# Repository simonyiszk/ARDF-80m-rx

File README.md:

# ARDF-80m-rx
Rókavevő a 80m-es rádióamatőr sávra (3579 kHz fix frekvenciájú)

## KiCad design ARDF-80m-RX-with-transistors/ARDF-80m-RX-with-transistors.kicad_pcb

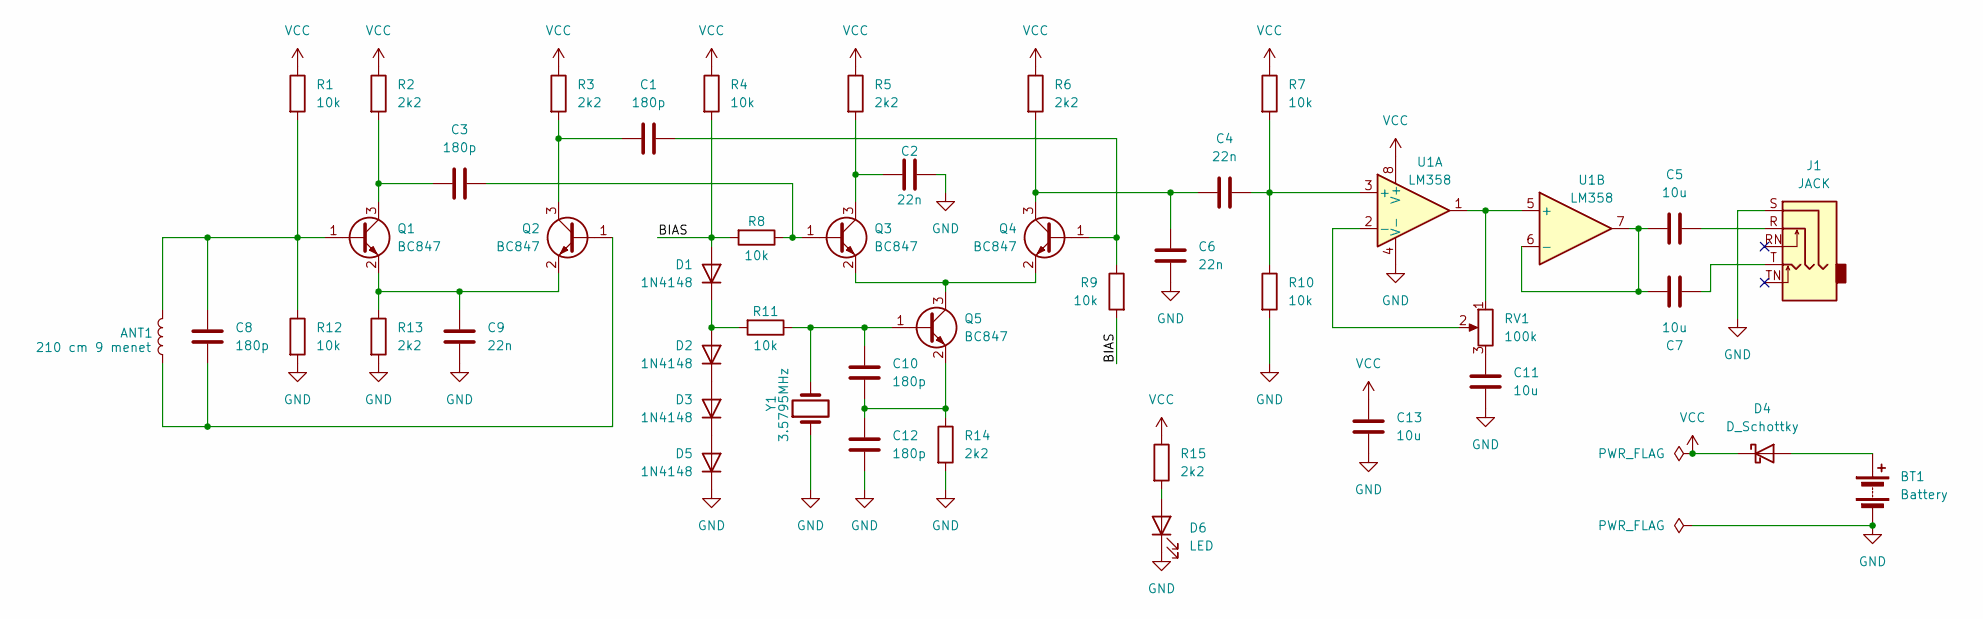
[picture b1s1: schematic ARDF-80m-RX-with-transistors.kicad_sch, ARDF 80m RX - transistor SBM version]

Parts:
ANT1: 210 cm 9 menet; PinHeader_2x01_P2.54mm_Vertical
BT1: Battery; PinHeader_2x01_P2.54mm_Vertical
C1, C3, C8, C10, C12: 180p; C_0805_2012Metric_Pad1.18x1.45mm_HandSolder
C2, C4, C6, C9: 22n; C_0805_2012Metric_Pad1.18x1.45mm_HandSolder
C5, C7, C11, C13: 10u; C_0805_2012Metric_Pad1.18x1.45mm_HandSolder
D1, D2, D3, D5: 1N4148; D_0805_2012Metric_Pad1.15x1.40mm_HandSolder
D4: D_Schottky; D_SMB_Handsoldering
D6: LED; LED_D3.0mm
J1: JACK; Jack_3.5mm_CUI_SJ1-3525N_Horizontal
Q1, Q2, Q3, Q4, Q5: BC847; SOT-23
R1, R4, R7, R8, R9, R10, R11, R12: 10k; R_0805_2012Metric_Pad1.20x1.40mm_HandSolder
R2, R3, R5, R6, R13, R14, R15: 2k2; R_0805_2012Metric_Pad1.20x1.40mm_HandSolder
RV1: 100k; Potentiometer_ACP_CA9-V10_Vertical
U1: LM358; SOIC-8_3.9x4.9mm_P1.27mm
Y1: 3.5795MHz; Crystal_HC49-4H_Vertical

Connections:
/BIAS: D1.2 (A), R4.2, R8.2, R9.2
GND: BT1.2 (-), C2.2, C6.2, C9.2, C11.2, C12.2, C13.1, D5.1 (K), D6.1 (K), J1.S, R10.2, R12.2, R13.2, R14.2, U1.4 (V-), Y1.1
unnamed: BT1.1 (+), D4.2 (A)
unnamed: C5.2, J1.R
unnamed: C7.1, J1.T
unnamed: C11.1, RV1.3
unnamed: D1.1 (K), D2.2 (A), R11.2
unnamed: D2.1 (K), D3.2 (A)
unnamed: D3.1 (K), D5.2 (A)
unnamed: D6.2 (A), R15.2
unnamed: ANT1.2, C8.1, Q1.1 (B), R1.2, R12.1
unnamed: C3.2, Q1.3 (C), R2.2
unnamed: C9.1, Q1.2 (E), Q2.2 (E), R13.1
unnamed: ANT1.1, C8.2, Q2.1 (B)
unnamed: C1.1, Q2.3 (C), R3.2
unnamed: C3.1, Q3.1 (B), R8.1
unnamed: C2.1, Q3.3 (C), R5.2
unnamed: Q3.2 (E), Q4.2 (E), Q5.3 (C)
unnamed: C1.2, Q4.1 (B), R9.1
unnamed: C4.1, C6.1, Q4.3 (C), R6.2
unnamed: C10.1, Q5.1 (B), R11.1, Y1.2
unnamed: C10.2, C12.1, Q5.2 (E), R14.1
unnamed: C4.2, R7.2, R10.1, U1.3 (+)
unnamed: RV1.2, U1.2 (-)
unnamed: RV1.1, U1.1, U1.5 (+)
unnamed: C5.1, C7.2, U1.6 (-), U1.7
VCC: C13.2, D4.1 (K), R1.1, R2.1, R3.1, R4.1, R5.1, R6.1, R7.1, R15.1, U1.8 (V+)

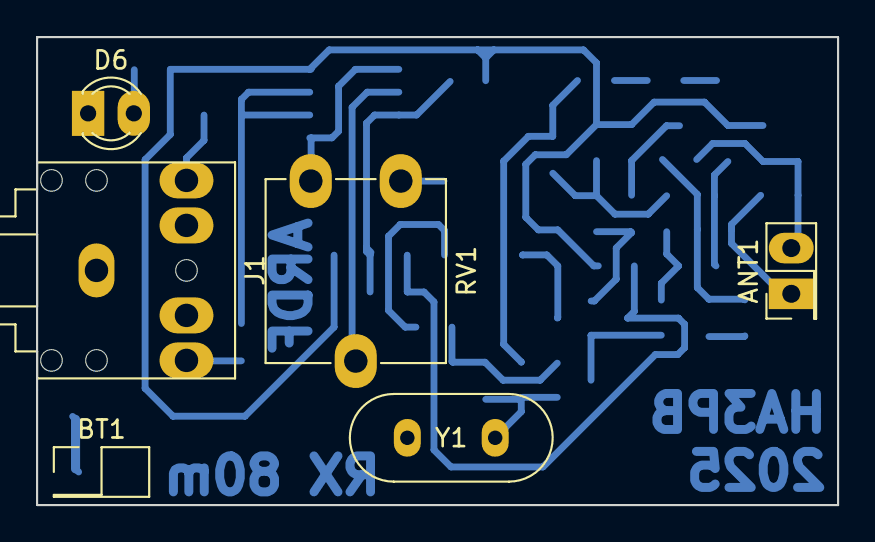
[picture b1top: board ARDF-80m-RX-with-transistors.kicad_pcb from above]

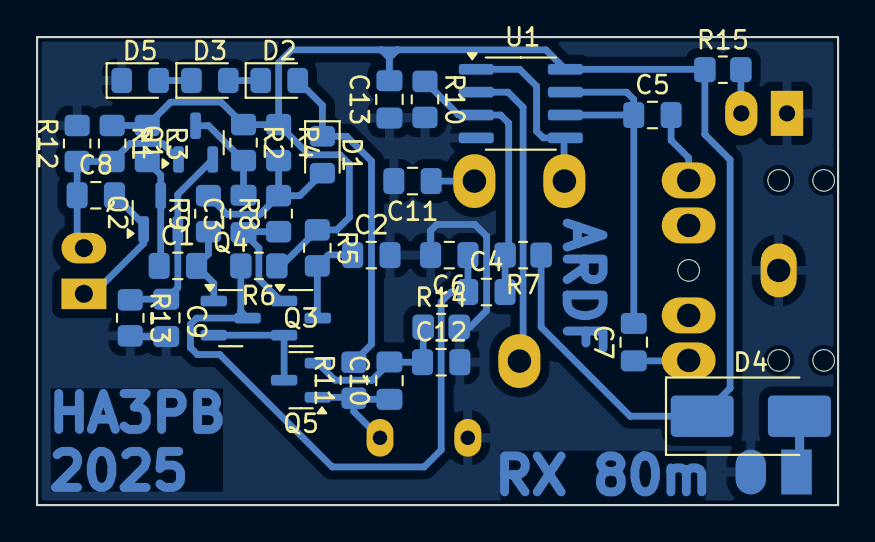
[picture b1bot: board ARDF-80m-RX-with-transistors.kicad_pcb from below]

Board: 2 copper layers, 44.5 x 26.0 mm, 45 parts (39 on the bottom side), 27 nets.

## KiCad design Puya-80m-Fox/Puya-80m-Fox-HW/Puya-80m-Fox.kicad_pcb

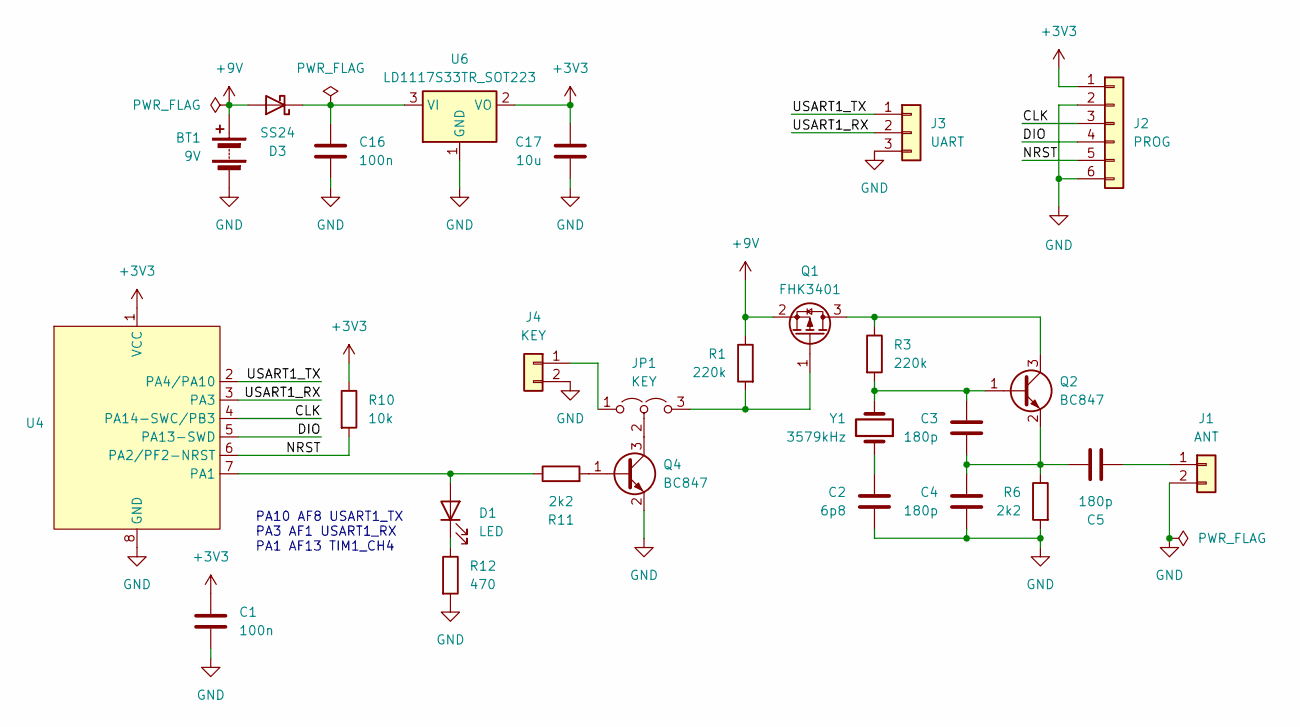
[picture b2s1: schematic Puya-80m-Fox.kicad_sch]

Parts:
BT1: 9V; PinHeader_1x02_P2.54mm_Vertical
C1, C16: 100n; C_0805_2012Metric_Pad1.18x1.45mm_HandSolder
C2: 6p8; C_0805_2012Metric_Pad1.18x1.45mm_HandSolder
C3, C4, C5: 180p; C_0805_2012Metric_Pad1.18x1.45mm_HandSolder
C17: 10u; C_0805_2012Metric_Pad1.18x1.45mm_HandSolder
D1: LED; LED_0805_2012Metric_Pad1.15x1.40mm_HandSolder
D3: SS24; D_SMA
J1: ANT; PinHeader_1x02_P2.54mm_Vertical
J2: PROG; PinHeader_1x06_P2.54mm_Vertical
J3: UART; PinHeader_1x03_P2.54mm_Vertical
J4: KEY; PinHeader_1x02_P2.54mm_Vertical
JP1: KEY; SolderJumper-3_P1.3mm_Open_RoundedPad1.0x1.5mm
Q1: FHK3401; SOT-23
Q2, Q4: BC847; SOT-23
R1, R3: 220k; R_0805_2012Metric_Pad1.20x1.40mm_HandSolder
R6, R11: 2k2; R_0805_2012Metric_Pad1.20x1.40mm_HandSolder
R10: 10k; R_0805_2012Metric_Pad1.20x1.40mm_HandSolder
R12: 470; R_0805_2012Metric_Pad1.20x1.40mm_HandSolder
U4: SOP-8_3.9x4.9mm_P1.27mm
U6: LD1117S33TR_SOT223; SOT-223-3_TabPin2
Y1: 3579kHz; Crystal_HC49-4H_Vertical

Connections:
+3V3: C1.1, C17.1, J2.1, R10.1, U4.1 (VCC), U6.2 (VO)
+9V: BT1.1 (+), D3.2 (A), Q1.2 (S), R1.1
/CLK: J2.3, U4.4 (PA14-SWC/PB3)
/DIO: J2.4, U4.5 (PA13-SWD)
/NRST: J2.5, R10.2, U4.6 (PA2/PF2-NRST)
/USART1_RX: J3.2, U4.3 (PA3)
/USART1_TX: J3.1, U4.2 (PA4/PA10)
GND: BT1.2 (-), C1.2, C2.2, C4.2, C16.2, C17.2, J1.2, J2.2, J2.6, J3.3, J4.2, Q4.2 (E), R6.2, R12.2, U4.8 (GND), U6.1 (GND)
unnamed: C2.1, Y1.1
unnamed: D1.2 (A), R11.1, U4.7 (PA1)
unnamed: D1.1 (K), R12.1
unnamed: C16.1, D3.1 (K), U6.3 (VI)
unnamed: C5.2, J1.1
unnamed: J4.1, JP1.1 (A)
unnamed: JP1.3 (B), Q1.1 (G), R1.2
unnamed: JP1.2 (C), Q4.3 (C)
unnamed: Q1.3 (D), Q2.3 (C), R3.1
unnamed: C3.1, Q2.1 (B), R3.2, Y1.2
unnamed: C3.2, C4.1, C5.1, Q2.2 (E), R6.1
unnamed: Q4.1 (B), R11.2

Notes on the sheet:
PA10 AF8 USART1_TX PA3 AF1 USART1_RX PA1 AF13 TIM1_CH4

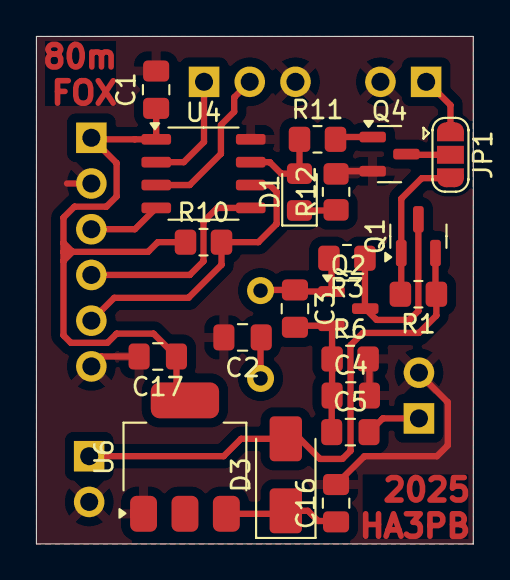
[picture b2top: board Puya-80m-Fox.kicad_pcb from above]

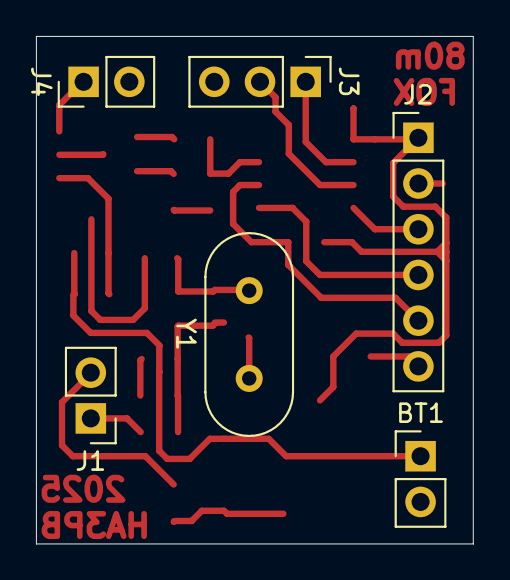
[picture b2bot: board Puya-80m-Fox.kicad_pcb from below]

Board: 2 copper layers, 24.3 x 28.2 mm, 27 parts (6 on the bottom side), 20 nets.

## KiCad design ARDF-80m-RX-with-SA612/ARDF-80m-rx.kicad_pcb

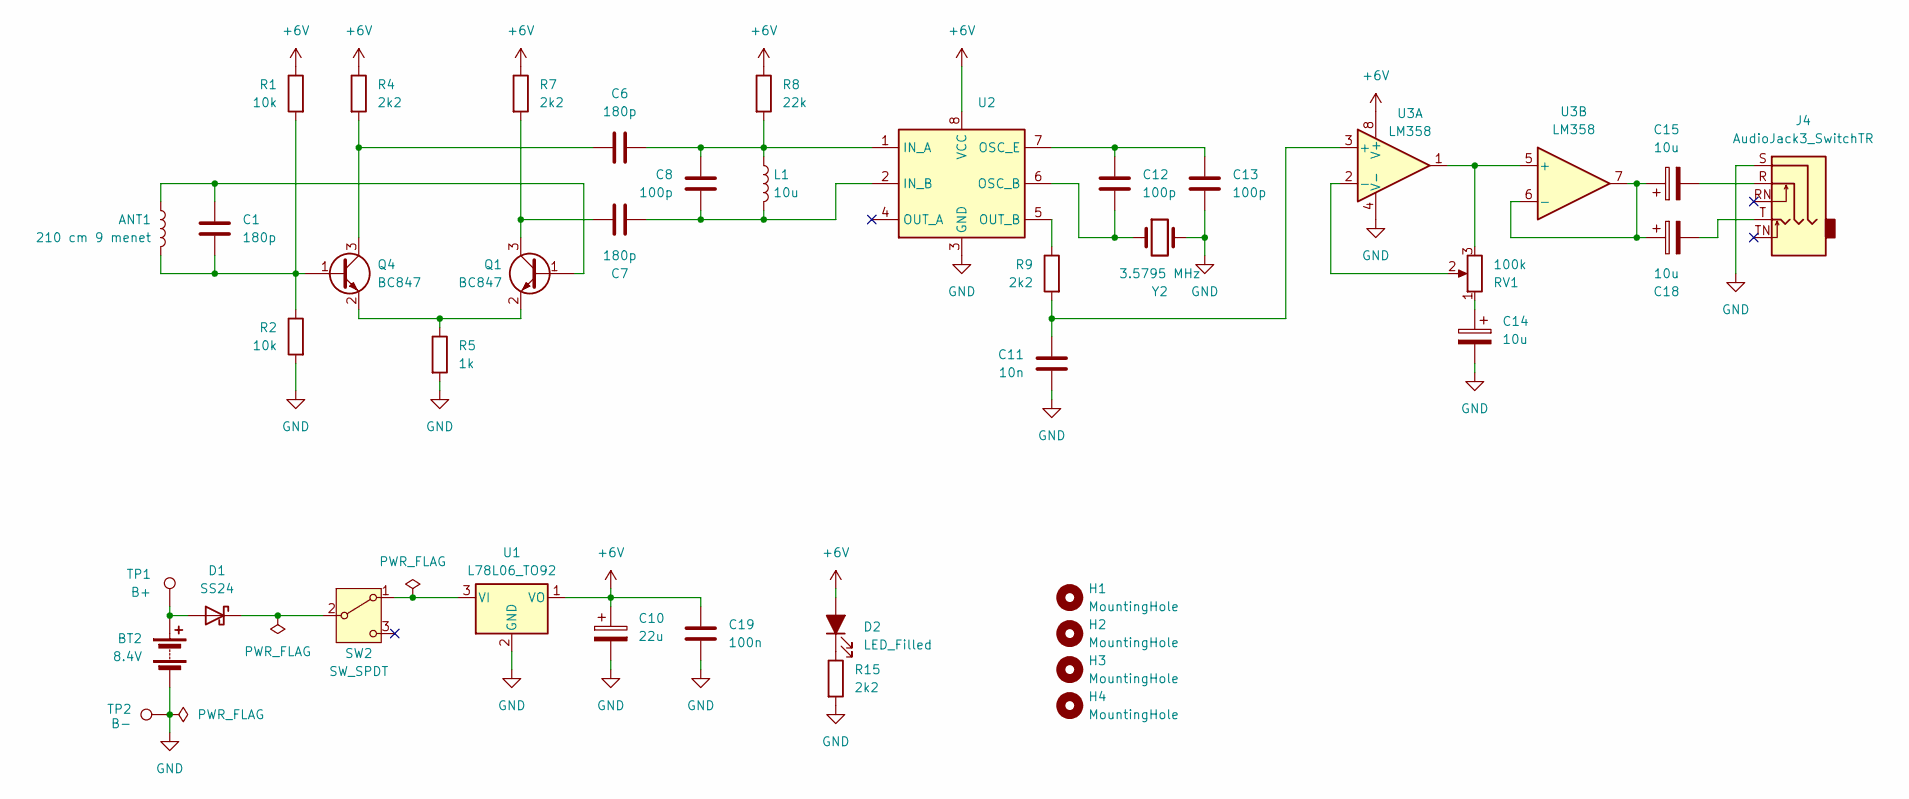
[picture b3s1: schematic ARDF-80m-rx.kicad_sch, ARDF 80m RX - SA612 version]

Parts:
ANT1: 210 cm 9 menet; PinHeader_1x02_P2.54mm_Vertical
BT2: 8.4V; BarrelJack_GCT_DCJ200-10-A_Horizontal
C1, C6, C7: 180p; C_0805_2012Metric_Pad1.18x1.45mm_HandSolder
C8, C12, C13: 100p; C_0805_2012Metric_Pad1.18x1.45mm_HandSolder
C10: 22u; C_0805_2012Metric_Pad1.18x1.45mm_HandSolder
C11: 10n; C_0805_2012Metric_Pad1.18x1.45mm_HandSolder
C14, C15, C18: 10u; C_0805_2012Metric_Pad1.18x1.45mm_HandSolder
C19: 100n; C_0805_2012Metric_Pad1.18x1.45mm_HandSolder
D1: SS24; D_SMA
D2: LED_Filled; LED_D5.0mm
H1, H2, H3, H4: MountingHole; MountingHole_2.7mm_M2.5
J4: AudioJack3_SwitchTR; Jack_3.5mm_CUI_SJ1-3525N_Horizontal
L1: 10u; L_0805_2012Metric_Pad1.15x1.40mm_HandSolder
Q1, Q4: BC847; SOT-23
R1, R2: 10k; R_0805_2012Metric_Pad1.20x1.40mm_HandSolder
R4, R7, R9, R15: 2k2; R_0805_2012Metric_Pad1.20x1.40mm_HandSolder
R5: 1k; R_0805_2012Metric_Pad1.20x1.40mm_HandSolder
R8: 22k; R_0805_2012Metric_Pad1.20x1.40mm_HandSolder
RV1: 100k; Potentiometer_ACP_CA9-V10_Vertical
SW2: SW_SPDT; SW_Push_2P2T_Toggle_CK_PVA2OAH5xxxxxxV2
TP1: B+; TestPoint_Pad_3.0x3.0mm
TP2: B-; TestPoint_Pad_3.0x3.0mm
U1: L78L06_TO92; TO-92_Inline
U2: (no value)
U3: LM358; SOIC-8_3.9x4.9mm_P1.27mm
Y2: 3.5795 MHz; Crystal_HC49-4H_Vertical

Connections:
+6V: C10.1, C19.1, D2.2 (A), R1.1, R4.1, R7.1, R8.1, U1.1 (VO), U2.8 (VCC), U3.8 (V+)
GND: BT2.2 (-), C10.2, C11.2, C13.2, C14.2, C19.2, J4.S, R2.2, R5.2, R15.2, TP2.1, U1.2 (GND), U2.3 (GND), U3.4 (V-), Y2.2
unnamed: C14.1, RV1.1
unnamed: C15.2, J4.R
unnamed: C18.2, J4.T
unnamed: BT2.1 (+), D1.2 (A), TP1.1
unnamed: D1.1 (K), SW2.2 (B)
unnamed: D2.1 (K), R15.1
unnamed: ANT1.1, C1.1, Q1.1 (B)
unnamed: C7.1, Q1.3 (C), R7.2
unnamed: Q1.2 (E), Q4.2 (E), R5.1
unnamed: ANT1.2, C1.2, Q4.1 (B), R1.2, R2.1
unnamed: C6.1, Q4.3 (C), R4.2
unnamed: SW2.1 (A), U1.3 (VI)
unnamed: C6.2, C8.1, L1.1, R8.2, U2.1 (IN_A)
unnamed: C7.2, C8.2, L1.2, U2.2 (IN_B)
unnamed: C12.2, U2.6 (OSC_B), Y2.1
unnamed: C12.1, C13.1, U2.7 (OSC_E)
unnamed: R9.1, U2.5 (OUT_B)
unnamed: C11.1, R9.2, U3.3 (+)
unnamed: RV1.2, U3.2 (-)
unnamed: RV1.3, U3.1, U3.5 (+)
unnamed: C15.1, C18.1, U3.6 (-), U3.7

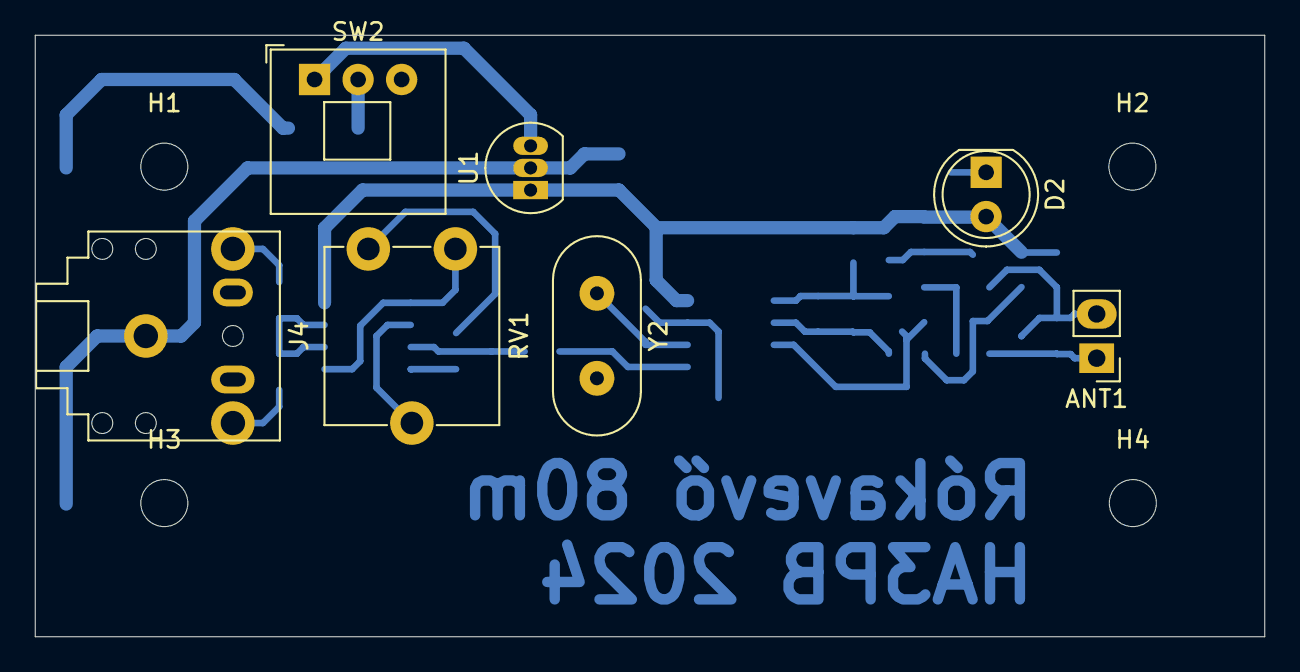
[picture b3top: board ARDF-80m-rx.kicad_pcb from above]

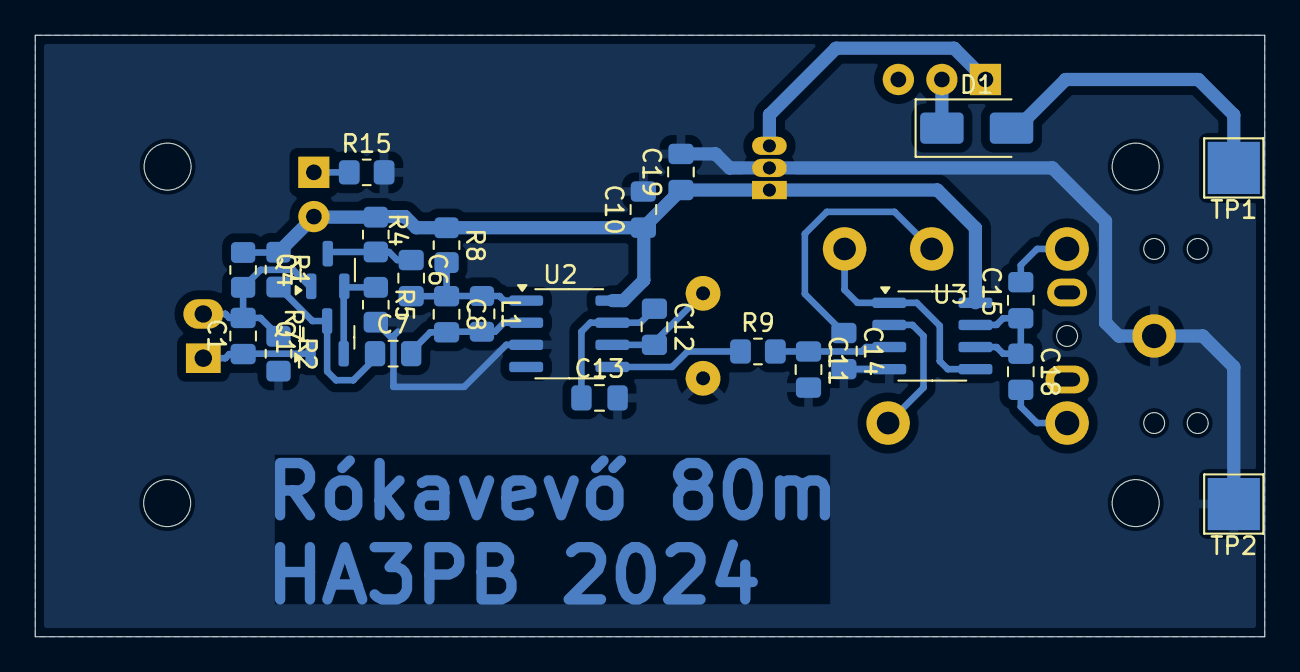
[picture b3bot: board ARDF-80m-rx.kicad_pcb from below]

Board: 2 copper layers, 70.6 x 34.5 mm, 39 parts (28 on the bottom side), 23 nets.

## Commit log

2025-06-03 Add design files of current version
2025-06-03 Update README.md
    Add image in README
2025-06-03 Add interactive BOM
2025-06-12 Restructure project files
2025-06-22 Add prototype of foxoring beacon
2025-06-28 Add receiver board with transistor single balanced mixer
2025-06-28 Add schematic and PCB pdf exports and interactive BOM
2025-06-29 Update diodes packaging
2025-06-29 Update jack connector footprint
2025-06-30 PCB export
